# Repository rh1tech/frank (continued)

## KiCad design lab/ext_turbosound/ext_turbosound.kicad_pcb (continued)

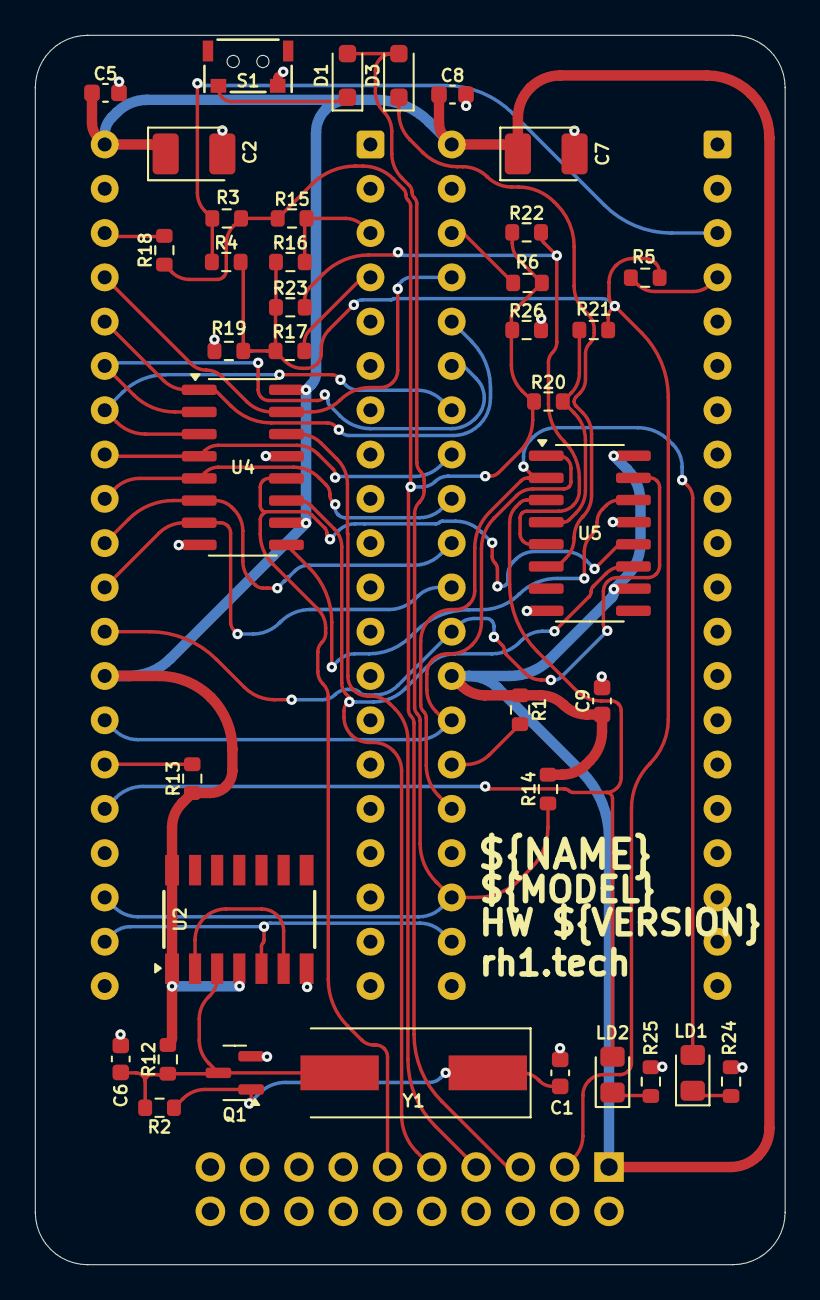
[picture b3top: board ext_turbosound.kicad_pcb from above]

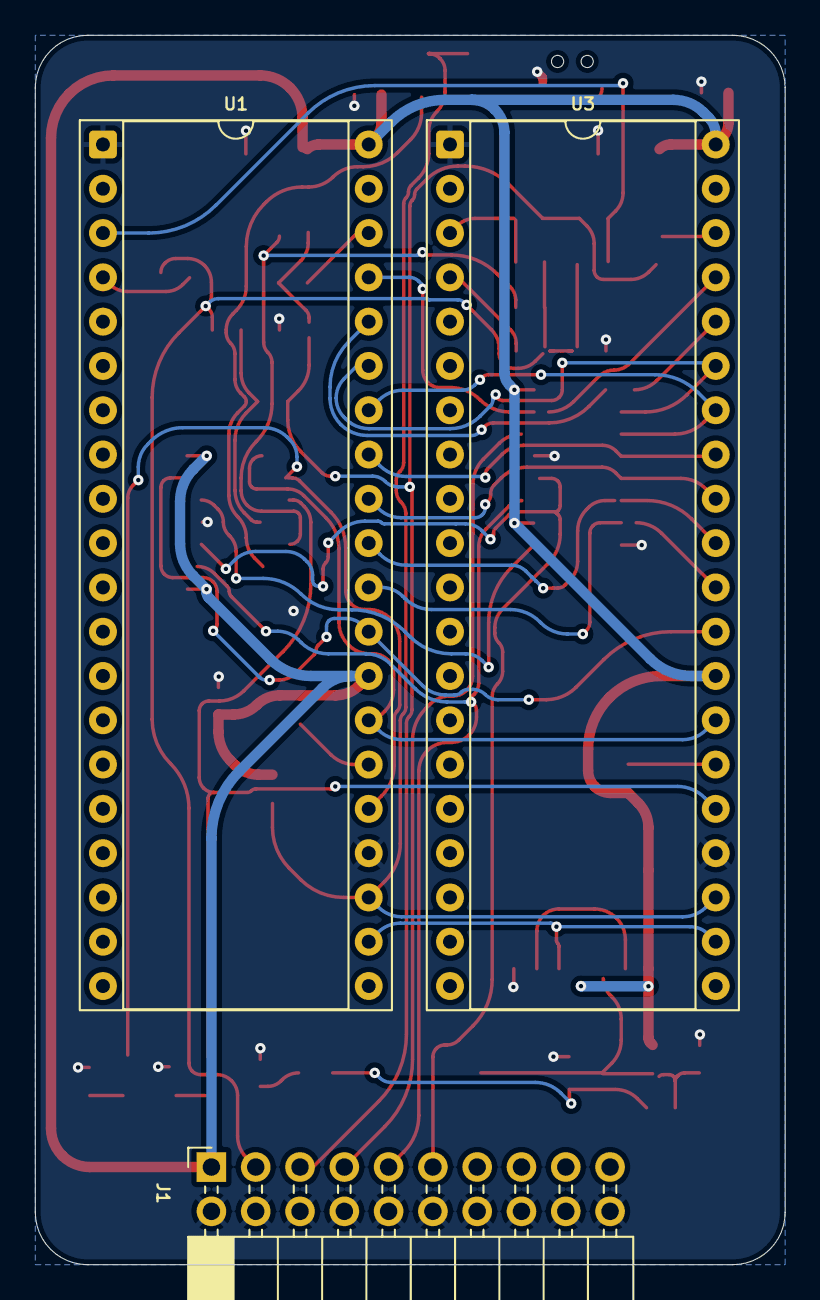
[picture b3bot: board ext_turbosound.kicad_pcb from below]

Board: 2 copper layers, 43.0 x 70.5 mm, 41 parts (3 on the bottom side), 39 nets.

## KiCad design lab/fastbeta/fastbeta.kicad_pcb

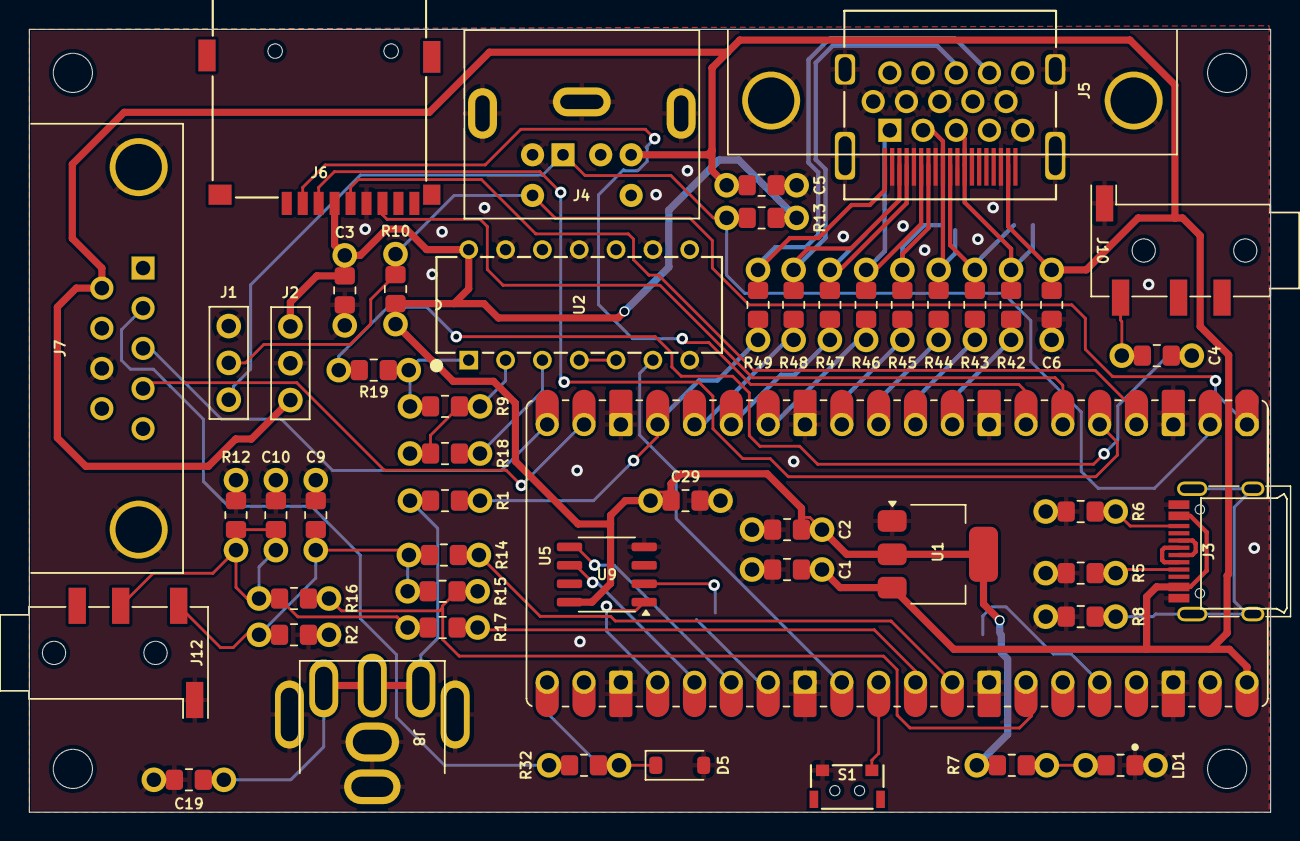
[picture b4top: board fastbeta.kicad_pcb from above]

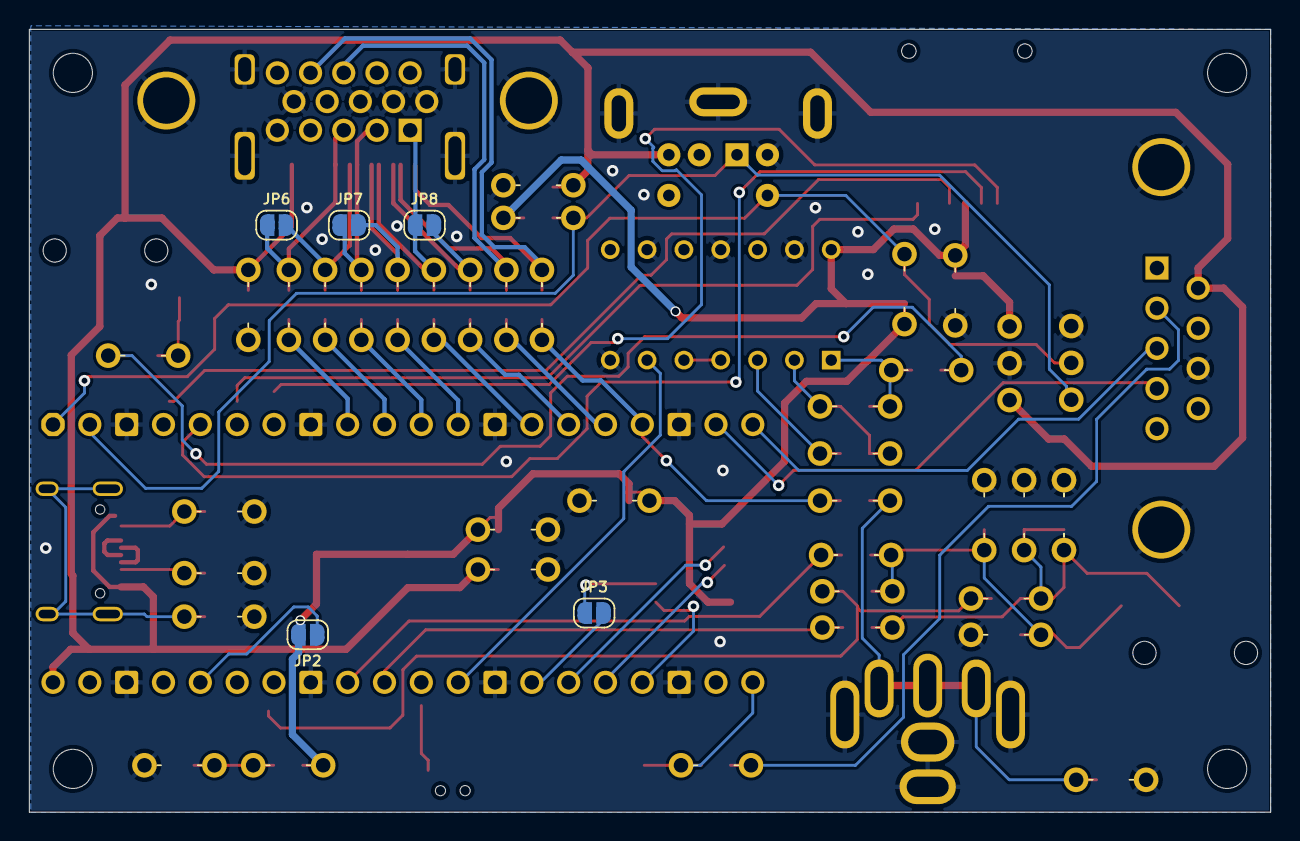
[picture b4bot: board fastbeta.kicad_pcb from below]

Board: 2 copper layers, 85.6 x 54.0 mm, 62 parts (5 on the bottom side), 55 nets.

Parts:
C1, C2: 10u; Combined 0805 CR
C3, C4, C5, C6, C29: 100n; Combined 0805 CR
C9, C10: 10n; Combined 0805 CR
C19: 470pF; Combined 0805 CR
D5: 3V3; Diode (SOD-123)
H1, H2, H3, H4: Hole 2.7mm; Mounting Hole (2.7mm)
J1, J2: Pin Header 1x03; Pin Header (1x03)
J3: USB4215; USB Type C
J4: MDC-036; MiniDIN (6 Pin, female)
J5: D-SUB 15 Female; D-SUB (15 pin, female)
J6: 104031-0811; MicroSD (SMD, long)
J7: D-SUB 9 Male; D-SUB (9 pin, male, top mount)
J8: RCA-103; RCA
J9: DC3RX19JA2; HDMI (female)
J10, J12: PJ-320D; Jack (3.5mm, PJ-320D)
JP2, JP3, JP6, JP7, JP8: Jumper (Solder); Jumper (solder)
LD1: Green; Combined 0805 LD
R1: 75R; Combined 0805 RE
R2, R12: 330R; Combined 0805 RE
R5, R6: 5.1K; Combined 0805 RE
R7, R10, R13, R14, R17, R32: 1K; Combined 0805 RE
R8: 1M; Combined 0805 RE
R9, R18: 100K; Combined 0805 RE
R15, R16: 2K; Combined 0805 RE
R19: 4.7K; Combined 0805 RE
R42, R43, R44, R45, R46, R47, R48, R49: 220R; Combined 0805 RE
S1: Reset RP2530A; TACT-SIDE-4623
U1: NCP1117 3.3; SOT-223
U2: N14; CD4069UBE
U5: Rasberry Pi Pico; Raspberry Pi Pico
U9: ESP-PSRAM32; SO-8

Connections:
+3V3: C2.1, C3.2, C29.1, J2.1, J6.4 (VDD), JP2.2 (B), R7.2, R10.2, R13.2, U1.2 (VO), U2.14 (VDD), U9.8 (VCC)
/Audio/L: C9.1, J12.T, R2.1, R14.1, R15.1
/Audio/R: C10.1, J12.R, R12.1, R16.1, R17.1
/PGPIO0: J1.2, J4.5, R10.1, U5.1 (GPIO0)
/PGPIO1: J1.3, J4.1, R13.1, U5.2 (GPIO1)
/PGPIO2: J6.5 (CLK), U5.4 (GPIO2)
/PGPIO3: J6.3 (CMD), U5.5 (GPIO3)
/PGPIO4: J6.7 (DAT0), U5.6 (GPIO4)
/PGPIO5: J6.2 (DAT3/CD), U5.7 (GPIO5)
/PGPIO6: R42.2, U5.9 (GPIO6)
/PGPIO7: R43.2, U5.10 (GPIO7)
/PGPIO8: R44.2, U5.11 (GPIO8)
/PGPIO9: R45.2, U5.12 (GPIO9)
/PGPIO10: R46.2, U5.14 (GPIO10)
/PGPIO11: R47.2, U5.15 (GPIO11)
/PGPIO12: R48.2, U5.16 (GPIO12)
/PGPIO13: R1.1, R49.2, U5.17 (GPIO13)
/PGPIO14: J7.4, U5.19 (GPIO14)
/PGPIO15: J7.3, U5.20 (GPIO15)
/PGPIO16: D5.1 (K), R32.1, U5.21 (GPIO16)
/PGPIO18: U5.24 (GPIO18), U9.1 (~CE)
/PGPIO19: U5.25 (GPIO19), U9.6 (SCLK)
/PGPIO20: U5.26 (GPIO20), U9.5 (SI/SIO)
/PGPIO21: JP3.2 (B), U5.27 (GPIO21)
/PGPIO22: U2.6 (I=*C), U5.29 (GPIO22)
/PGPIO26: R17.2, U5.31 (GPIO26_ADC0)
/PGPIO27: R14.2, U5.32 (GPIO27_ADC1)
/PGPIO28: R15.2, R16.2, U5.34 (GPIO28_ADC2)
/PRUN: S1.1, U5.30 (RUN)
/Power/D+: J3.6 (DP1), J3.8 (DP2)
/Power/D-: J3.5 (DN2), J3.7 (DN1)
/Tape In/TAPE: C4.2, J10.T
/Video Out/VGA_B: J5.3, J9.12 (CLKN), JP6.1 (A), R42.1
/Video Out/VGA_BH: J9.10 (CLKP), JP6.2 (B), R43.1
/Video Out/VGA_G: J5.2, J9.9 (D0N), JP7.1 (A), R44.1
/Video Out/VGA_GH: J9.7 (D0P), JP7.2 (B), R45.1
/Video Out/VGA_HS: J5.13, J9.3 (D2N), R48.1
/Video Out/VGA_R: J5.1, J9.6 (D1N), JP8.1 (A), R46.1
/Video Out/VGA_RH: J9.4 (D1P), JP8.2 (B), R47.1
/Video Out/VGA_VS: J5.14, J9.1 (D2P), R49.1
GND: C1.2, C2.2, C3.1, C5.2, C6.2, C9.2, C10.2, C19.2, C29.2, D5.2 (A), J1.1, J2.2, J3.1 (GND), J3.12 (GND), J4.3, J5.0, J5.5, J5.6, J5.7, J5.8, J5.10, J6.6 (VSS), J7.8, J8.2, J9.2 (G_D2), J9.5 (G_D1), J9.8 (G_D0), J9.11 (G_CLK), J9.17 (G_DDC/CEC), J9.20 (SHIELD1), J9.21 (SHIELD2), J9.22 (SHIELD3), J9.23 (SHIELD4), J10.S, J12.S, LD1.1 (K), R2.2, R5.1, R6.1, R8.2, R12.2, S1.2, U1.1 (GND), U2.7 (VSS), U2.9 (D14), U2.11 (E), U2.13 (F), U5.3 (GND), U5.8 (GND), U5.13 (GND), U5.18 (GND), U5.23 (GND), U5.28 (GND), U5.33 (AGND), U5.38 (GND), U9.4 (VSS)
unnamed: C4.1, R19.2
unnamed: J3.4 (CC1), R5.2
unnamed: J3.10 (CC2), R6.2
unnamed: J3.13 (SHIELD), R8.1
unnamed: J7.2, R32.2
unnamed: C19.1, J8.1, R1.2
unnamed: JP2.1 (A), U5.36 (3V3)
unnamed: JP3.1 (A), U9.2 (SO/SIO)
unnamed: LD1.2 (A), R7.1
unnamed: R9.2, R19.1, U2.1 (A)
unnamed: R18.1, U2.3 (B)
unnamed: U2.4 (H=*B), U2.5 (C)
unnamed: R9.1, R18.2, U2.2 (G-*A)
VBUS: C1.1, C5.1, C6.1, J2.3, J3.2 (VBUS), J3.11 (VBUS), J4.4, J7.6, J9.18 (+5V), U1.3 (VI), U5.40 (VBUS)

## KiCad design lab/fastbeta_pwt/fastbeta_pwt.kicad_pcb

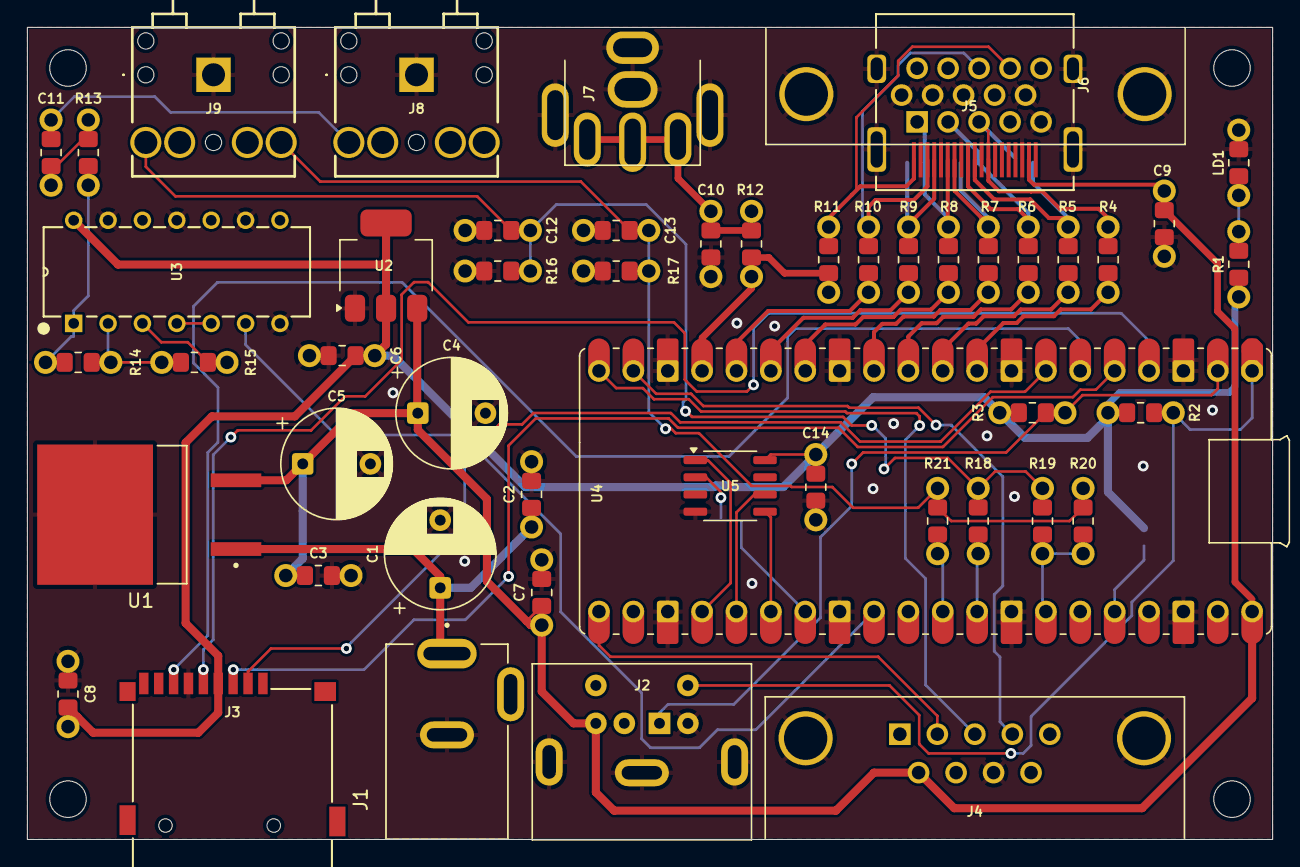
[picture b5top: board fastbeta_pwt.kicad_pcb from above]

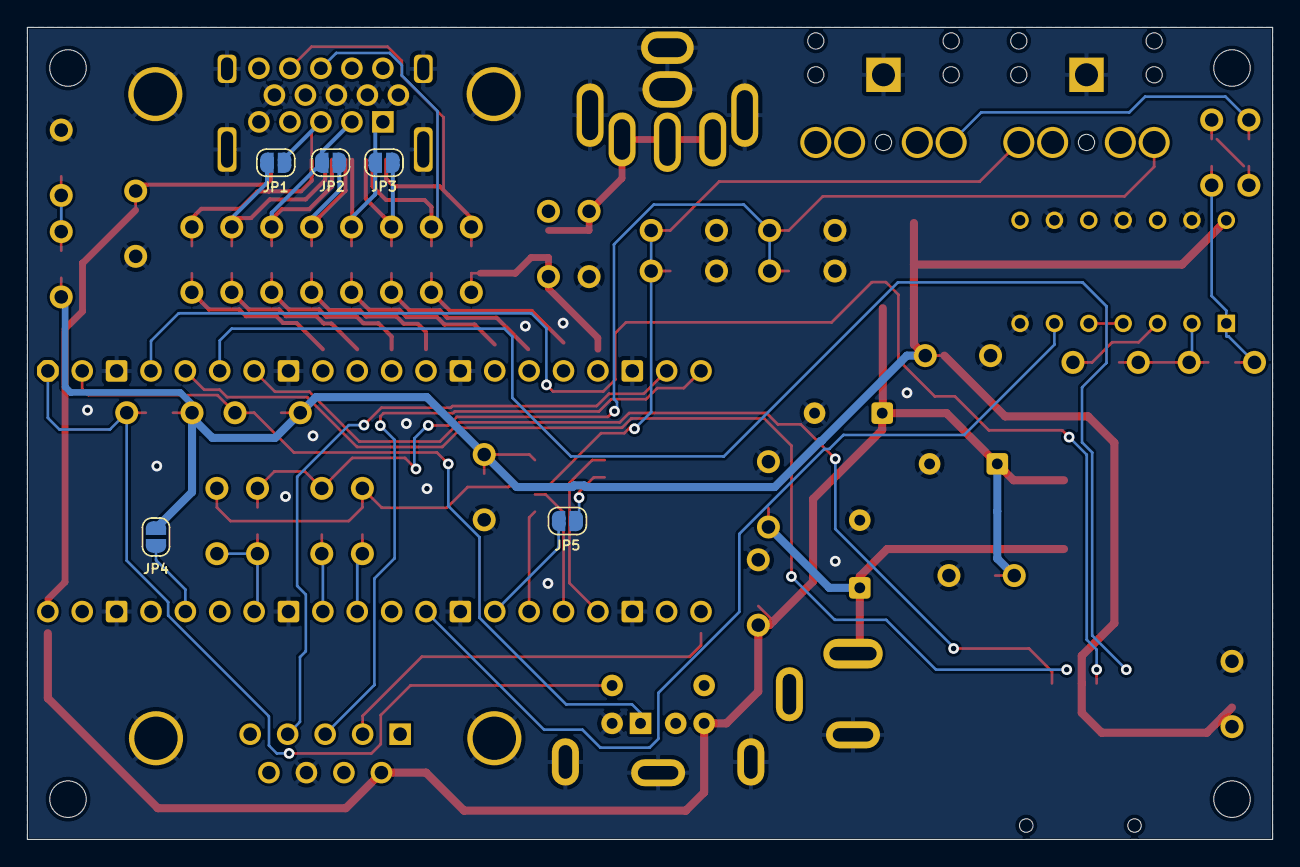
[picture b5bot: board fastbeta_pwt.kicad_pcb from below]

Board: 2 copper layers, 92.0 x 60.0 mm, 59 parts (5 on the bottom side), 49 nets.

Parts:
C1, C4, C5: 470u; Capacitor (radial, polar, D8.0mm, P5.00mm)
C2, C3, C7, C8, C9, C11, C14: 100n; Combined 0805 CR
C6: 10u; Combined 0805 CR
C10: 470pF; Combined 0805 CR
C12, C13: 10n; Combined 0805 CR
H1, H2, H3, H4: Hole 2.7mm; Mounting Hole (2.7mm)
J1: DC-005-5A-2.0; XKB_DC-005-5A-2.0
J2: MDC-036; MiniDIN (6 Pin, female)
J3: 104031-0811; MicroSD (SMD, long)
J4: D-SUB 9 Male; D-SUB (9 pin, male, top mount)
J5: DC3RX19JA2; HDMI (female)
J6: D-SUB 15 Female; D-SUB (15 pin, female)
J7: RCA-103; RCA
J8, J9: SJ1-3525N; SJ13525N
JP1, JP2, JP3, JP4, JP5: Jumper (Solder); Jumper (solder)
LD1: Green; Combined 0805 LD
R1, R2, R3, R18, R21: 1K; Combined 0805 RE
R4, R5, R6, R7, R8, R9, R10, R11: 220R; Combined 0805 RE
R12: 75R; Combined 0805 RE
R13: 4.7K; Combined 0805 RE
R14, R15: 100K; Combined 0805 RE
R16, R17: 330R; Combined 0805 RE
R19, R20: 2K; Combined 0805 RE
U1: L7805; TO254P1542X460-3N
U2: AMS1117 3.3; SOT-223
U3: CD4069UBE
U4: Rasberry Pi Pico; Raspberry Pi Pico
U5: ESP-PSRAM32; SO-8

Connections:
+3V3: C6.1, C8.2, C14.1, J3.4 (VDD), JP4.2 (B), R1.2, R2.2, R3.2, U2.2 (VO), U3.14 (VDD), U5.8 (VCC)
/Audio/L: C12.1, J9.2 (TIP), R16.1, R18.1, R19.1
/Audio/R: C13.1, J9.3 (RING), R17.1, R20.1, R21.1
/PGPIO0: J2.5, R2.1, U4.1 (GPIO0)
/PGPIO1: J2.1, R3.1, U4.2 (GPIO1)
/PGPIO2: J3.5 (CLK), U4.4 (GPIO2)
/PGPIO3: J3.3 (CMD), U4.5 (GPIO3)
/PGPIO4: J3.7 (DAT0), U4.6 (GPIO4)
/PGPIO5: J3.2 (DAT3/CD), U4.7 (GPIO5)
/PGPIO6: R4.2, U4.9 (GPIO6)
/PGPIO7: R5.2, U4.10 (GPIO7)
/PGPIO8: R6.2, U4.11 (GPIO8)
/PGPIO9: R7.2, U4.12 (GPIO9)
/PGPIO10: R8.2, U4.14 (GPIO10)
/PGPIO11: R9.2, U4.15 (GPIO11)
/PGPIO12: R10.2, U4.16 (GPIO12)
/PGPIO13: R11.2, R12.1, U4.17 (GPIO13)
/PGPIO14: J4.4, U4.19 (GPIO14)
/PGPIO15: J4.3, U4.20 (GPIO15)
/PGPIO16: J4.2, U4.21 (GPIO16)
/PGPIO18: U4.24 (GPIO18), U5.1 (~CE)
/PGPIO19: U4.25 (GPIO19), U5.6 (SCLK)
/PGPIO20: U4.26 (GPIO20), U5.5 (SI/SIO)
/PGPIO21: JP5.2 (B), U4.27 (GPIO21)
/PGPIO22: U3.6 (I=*C), U4.29 (GPIO22)
/PGPIO26: R21.2, U4.31 (GPIO26_ADC0)
/PGPIO27: R18.2, U4.32 (GPIO27_ADC1)
/PGPIO28: R19.2, R20.2, U4.34 (GPIO28_ADC2)
/Tape In/TAPE: C11.2, J8.2 (TIP)
/Video Out/VGA_B: J5.12 (CLKN), J6.3, JP1.1 (A), R4.1
/Video Out/VGA_BH: J5.10 (CLKP), JP1.2 (B), R5.1
/Video Out/VGA_G: J5.9 (D0N), J6.2, JP2.1 (A), R6.1
/Video Out/VGA_GH: J5.7 (D0P), JP2.2 (B), R7.1
/Video Out/VGA_HS: J5.3 (D2N), J6.13, R10.1
/Video Out/VGA_R: J5.6 (D1N), J6.1, JP3.1 (A), R8.1
/Video Out/VGA_RH: J5.4 (D1P), JP3.2 (B), R9.1
/Video Out/VGA_VS: J5.1 (D2P), J6.14, R11.1
GND: C1.2, C2.2, C3.2, C4.2, C5.2, C6.2, C7.2, C8.1, C9.2, C10.2, C12.2, C13.2, C14.2, J1.2, J2.3, J3.6 (VSS), J4.8, J5.2 (G_D2), J5.5 (G_D1), J5.8 (G_D0), J5.11 (G_CLK), J5.17 (G_DDC/CEC), J5.20 (SHIELD1), J5.21 (SHIELD2), J5.22 (SHIELD3), J5.23 (SHIELD4), J6.0, J6.5, J6.6, J6.7, J6.8, J6.10, J7.2, J8.1 (SLEEVE), J9.1 (SLEEVE), LD1.1 (K), R16.2, R17.2, U1.2 (GND), U2.1 (GND), U3.7 (VSS), U3.9 (D14), U3.11 (E), U3.13 (F), U4.3 (GND), U4.8 (GND), U4.13 (GND), U4.18 (GND), U4.23 (GND), U4.28 (GND), U4.33 (AGND), U4.38 (GND), U5.4 (VSS)
unnamed: C11.1, R13.2
unnamed: C10.1, J7.1, R12.2
unnamed: JP4.1 (A), U4.36 (3V3)
unnamed: JP5.1 (A), U5.2 (SO/SIO)
unnamed: LD1.2 (A), R1.1
unnamed: C1.1, C2.1, J1.1, U1.1 (IN)
unnamed: R13.1, R14.2, U3.1 (A)
unnamed: R15.1, U3.3 (B)
unnamed: U3.4 (H=*B), U3.5 (C)
unnamed: R14.1, R15.2, U3.2 (G-*A)
VBUS: C3.1, C4.1, C5.1, C7.1, C9.1, J2.4, J4.6, J5.18 (+5V), U1.3 (OUT), U2.3 (VI), U4.40 (VBUS)

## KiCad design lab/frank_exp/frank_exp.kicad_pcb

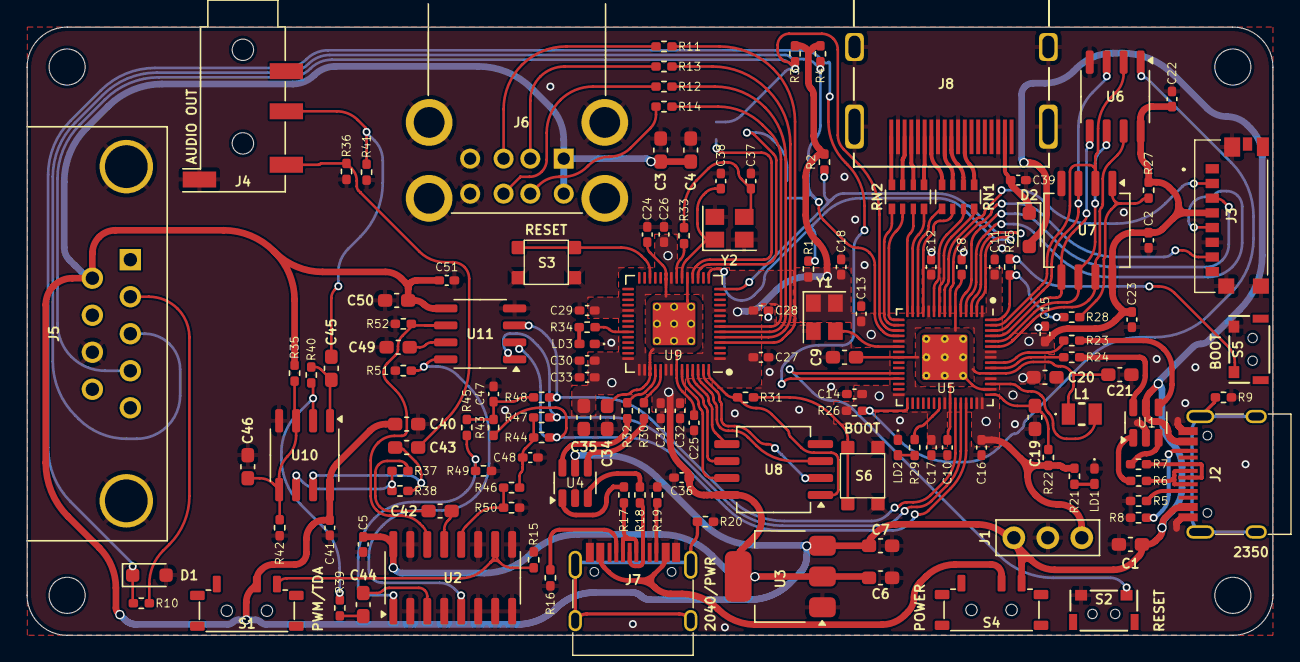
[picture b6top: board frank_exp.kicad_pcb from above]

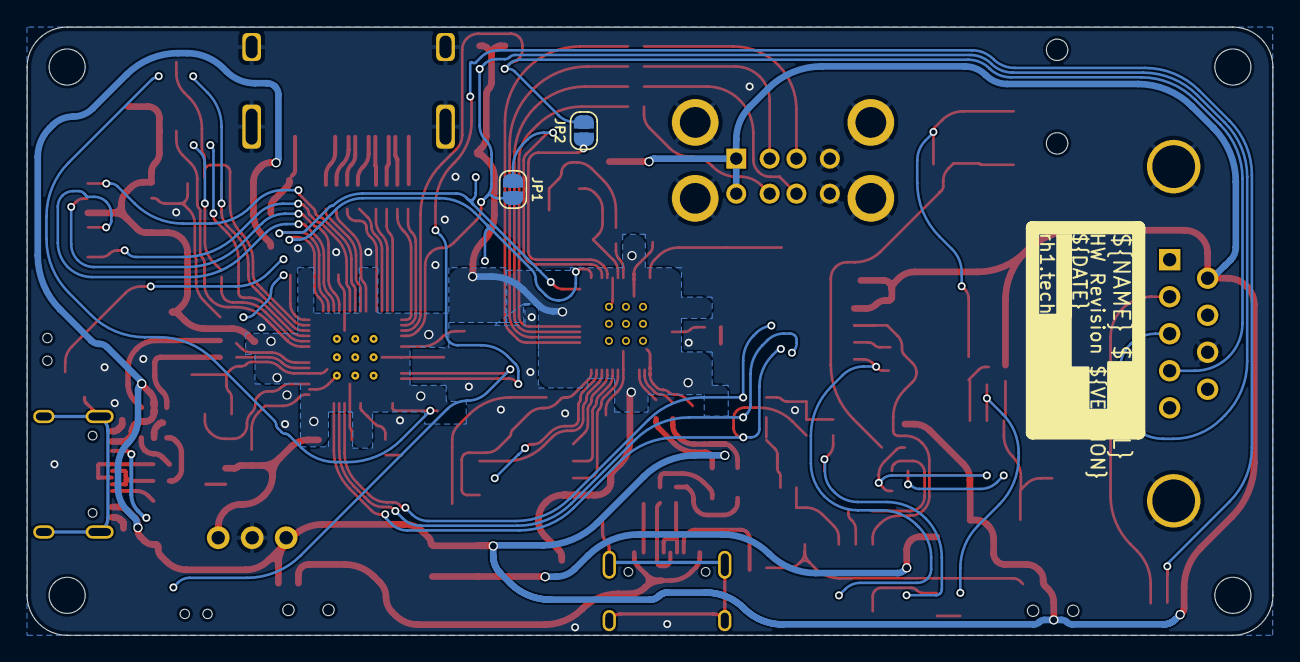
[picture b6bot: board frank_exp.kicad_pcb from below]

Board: 2 copper layers, 93.2 x 45.5 mm, 144 parts (2 on the bottom side), 116 nets.

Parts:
C1, C3, C4, C6, C7, C40, C42, C43, C44, C45, C46, C49, C50: 10u; Capacitor (0603)
C2, C5, C8, C10, C11, C12, C13, C14, C15, C16, C17, C18, C22, C23, C24, C25, C26, C27, C28, C29, C30, C31, C32, C33, C36, C39, C41, C51: 100n; Capacitor (0402)
C9, C19, C20, C21: 4.7u; Capacitor (0603)
C34, C35: 1u; Capacitor (0603)
C37, C38: 15p; Capacitor (0402)
C47, C48: 47n; Capacitor (0402)
D1: 3V3; Diode (SOD-323)
D2: 1N5819WS; Diode (SOD-323)
H1, H2, H3, H4: MountingHole; Mounting Hole (2.7mm)
J1: PWR; Pin Header (1x03)
J2, J7: USB4215-03-A; USB Type C
J3: 0475710001; MicroSD (SMD, short)
J4: PJ-320D; Jack (3.5mm, PJ-320D)
J5: D-SUB 9 Male; D-SUB (9 pin, male, top mount)
J6: SS-52100-004; USB Type A (stacked)
J8: DC3RX19JA2; HDMI (female)
JP1: Mouse (DATA); Jumper (solder)
JP2: Mouse (CLK); Jumper (solder)
L1: 3.3u; Inductor (0806)
LD1: Power; LED (0402)
LD2, LD3: Blue; LED (0402)
R1, R2, R3, R4, R15, R26, R27, R35, R37, R39, R42, R45, R46: 10K; Resistor (0402)
R5, R8, R16, R19: 5.1K; Resistor (0402)
R6, R7, R11, R12, R13, R14, R17, R18: 22R; Resistor (0402)
R9, R20: 1M; Resistor (0402)
R10, R21, R25, R29, R31, R33, R34, R47, R48: 1K; Resistor (0402)
R22: 33R; Resistor (0402)
R23, R24, R30, R32: 27R; Resistor (0402)
R28: 0R; Resistor (0402)
R36, R41: 20K; Resistor (0402)
R38, R40: 47K; Resistor (0402)
R43, R44, R49, R50: 2K; Resistor (0402)
R51, R52: 470R; Resistor (0402)
RN1, RN2: 270R; Resistor Array (4x0603)
S1, S4: MSK12C02; Switch (MSK12C02)
S2: Reset RP2530A; TACT-SIDE-4623
S3: Reset RP2040; Button (SMD, 3x3mm, 1-1)
S5: Boot 2350; TACT-SIDE-4623
S6: Boot 2040; Button (SMD, 3x3mm, 1-1)
U1, U4: USBLC6-2SC6; SOT-23-6
U2: 74HC4052D; SOP-16
U3: NCP1117 3.3; SOT-223
U5: RP2350; QFN 60 (RP2350A)
U6: ESP-PSRAM32; SO-8
U7: W25Q128JVS; SOIC-8
U8: W25Q128JVSIQ; SOIC-8
U9: RP2040; QFN 56
U10: LM358; SO-8
U11: TDA1387T; SO-8
Y1: ASE-12MHz; Crystal (3225, active)
Y2: 12 MHz; Crystal (3225)

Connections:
+1V1: C8.1, C9.1, C10.1, C21.1, L1.1, U5.6 (DVDD), U5.23 (DVDD), U5.39 (DVDD), U5.50 (VREG_FB)
+3V3: C2.2, C5.2, C6.1, C11.1, C12.1, C13.1, C14.1, C15.1, C16.1, C17.1, C18.1, C20.1, C22.1, C23.1, C26.1, C27.1, C28.1, C29.1, C30.1, C31.1, C32.1, C33.1, C35.1, C36.1, J1.1, J3.P4 (VDD), R1.2, R2.2, R3.2, R4.2, R21.2, R22.1, R26.2, R27.1, U2.16 (VCC), U3.2 (VO), U5.1 (IOVDD), U5.11 (IOVDD), U5.20 (IOVDD), U5.30 (IOVDD), U5.38 (IOVDD), U5.44 (ADC_AVDD), U5.45 (IOVDD), U5.49 (VREG_VIN), U5.53 (USB_OTP_VDD), U5.54 (QSPI_IOVDD), U6.8 (VCC), U7.8 (VCC), U8.8 (VCC), U9.1 (IOVDD), U9.10 (IOVDD), U9.22 (IOVDD), U9.33 (IOVDD), U9.42 (IOVDD), U9.43 (ADC_AVDD), U9.44 (VREG_IN), U9.48 (USB_VDD), U9.49 (IOVDD), Y1.1 (EN), Y1.4 (Vdd)
/AMP_IN_L: C42.1, U2.13 (1Z)
/AMP_IN_R: C44.1, U2.3 (2Z)
/AUDIOSW: R15.2, S1.3 (A), U2.10 (S0)
/Audio Out/AMP_OUTL: C43.2, J4.T, R36.2
/Audio Out/AMP_OUTR: C45.2, J4.R, R41.2
/D+: R23.1, U1.4 (I/O2)
/D-: R24.1, U1.6 (I/O1)
/GPIO0: R1.1, U5.2 (GPIO0), U9.15 (GPIO12)
/GPIO1: R2.1, U5.3 (GPIO1), U9.14 (GPIO11)
/GPIO2: J3.P5 (CLK), U5.4 (GPIO2)
/GPIO3: J3.P3 (CMD), U5.5 (GPIO3)
/GPIO4: J3.P7 (DAT0), U5.7 (GPIO4)
/GPIO5: J3.P2 (CD/DAT3), U5.8 (GPIO5)
/GPIO6: RN1.4 (R4.1), U5.9 (GPIO6)
/GPIO7: RN1.3 (R3.1), U5.10 (GPIO7)
/GPIO8: RN1.2 (R2.1), U5.12 (GPIO8)
/GPIO9: RN1.1 (R1.1), U5.13 (GPIO9)
/GPIO10: RN2.4 (R4.1), U5.14 (GPIO10)
/GPIO11: RN2.3 (R3.1), U5.15 (GPIO11)
/GPIO12: RN2.2 (R2.1), U5.16 (GPIO12)
/GPIO13: RN2.1 (R1.1), U5.17 (GPIO13)
/GPIO14: J5.4, JP2.2 (B), R3.1, U5.18 (GPIO14)
/GPIO15: J5.3, JP1.2 (B), R4.1, U5.19 (GPIO15)
/GPIO16: D1.1 (K), R10.1, U5.27 (GPIO16)
/GPIO19: R26.1, U5.31 (GPIO19), U6.1 (~CE)
/GPIO26: R48.2, U5.40 (GPIO26_ADC0), U11.3 (DATA)
/GPIO27: R47.2, U5.41 (GPIO27_ADC1), U11.1 (SCLK)
/GPIO28: R43.1, R44.1, U5.42 (GPIO28_ADC2), U11.2 (LRCK)
/MS_CLK: JP2.1 (A), U9.18 (GPIO15)
/MS_DATA: JP1.1 (A), U9.17 (GPIO14)
/PWM_OUT_L: R46.2, R50.1, U2.12 (1Y0)
/PWM_OUT_R: R45.2, R49.1, U2.1 (2Y0)
/RP2_D+: R30.1, U4.4 (I/O2)
/RP2_D-: R32.1, U4.6 (I/O1)
/RP2_GPIO2: R11.1, U9.4 (GPIO2)
/RP2_GPIO3: R13.1, U9.5 (GPIO3)
/RP2_GPIO4: R12.1, U9.6 (GPIO4)
/RP2_GPIO5: R14.1, U9.7 (GPIO5)
/RP2_RUN: S3.1, U9.26 (RUN)
/RP2040/GPIO25: R34.2, U9.37 (GPIO25)
/RP2040/QSPI_SCLK: U8.6 (CLK), U9.52 (QSPI_SCLK)
/RP2040/QSPI_SD0: U8.5 (DI(IO0)), U9.53 (QSPI_SD0)
/RP2040/QSPI_SD1: U8.2 (DO(IO1)), U9.55 (QSPI_SD1)
/RP2040/QSPI_SD2: U8.3 (IO2), U9.54 (QSPI_SD2)
/RP2040/QSPI_SD3: U8.7 (IO3), U9.51 (QSPI_SD3)
/RP2040/QSPI_SS: R31.1, U8.1 (~CS), U9.56 (QSPI_SS)
/RP2040/XIN: C38.1, U9.20 (XIN), Y2.1
/RP2040/XOUT: R33.1, U9.21 (XOUT)
/RP2350A/FLASH_SS: R27.2, R28.2, U7.1 (~CS)
/RP2350A/QSPI_SCLK: U5.56 (QSPI_SCLK), U6.6 (SCLK), U7.6 (CLK)
/RP2350A/QSPI_SD0: U5.57 (QSPI_SD0), U6.5 (SI/SIO), U7.5 (DI(IO0))
/RP2350A/QSPI_SD1: U5.59 (QSPI_SD1), U6.2 (SO/SIO), U7.2 (DO(IO1))
/RP2350A/QSPI_SD2: U5.58 (QSPI_SD2), U6.3 (SIO2), U7.3 (IO2)
/RP2350A/QSPI_SD3: U5.55 (QSPI_SD3), U6.7 (SIO3), U7.7 (IO3)
/RP2350A/QSPI_SS: R25.1, R28.1, U5.60 (QSPI_SS)
/RP2350A/VREG_AVDD: C19.1, R22.2, U5.46 (VREG_AVDD)
/RP2350A/VREG_LX: L1.2, U5.48 (VREG_LX)
/RP2350A/XIN: U5.21 (XIN), Y1.3 (OUT)
/RP2350A/~USB_BOOT: R25.2, S5.2
/RUN: S2.1, U5.26 (RUN)
/TDA_L: R52.2, U2.14 (1Y1), U11.6 (A_LEFT)
/TDA_R: R51.1, U2.5 (2Y1), U11.8 (A_RIGHT)
GND: C1.2, C2.1, C3.2, C4.2, C5.1, C6.2, C7.2, C8.2, C9.2, C10.2, C11.2, C12.2, C13.2, C14.2, C15.2, C16.2, C17.2, C18.2, C19.2, C20.2, C21.2, C22.2, C23.2, C24.2, C25.2, C26.2, C27.2, C28.2, C29.2, C30.2, C31.2, C32.2, C33.2, C34.2, C35.2, C36.2, C37.2, C38.2, C39.2, C40.1, C41.1, C46.1, C47.2, C48.2, C49.2, C50.2, C51.2, D1.2 (A), J1.2, J2.1 (GND), J2.12 (GND), J3.G1 (GND_1), J3.G2 (GND_2), J3.G3 (GND_3), J3.P6 (VSS), J4.S, J5.8, J6.4 (GND1), J6.8 (GND2), J6.9 (Shield), J7.1 (GND), J7.12 (GND), J8.2 (G_D2), J8.5 (G_D1), J8.8 (G_D0), J8.11 (G_CLK), J8.17 (G_DDC/CEC), J8.20 (SHIELD1), J8.21 (SHIELD2), J8.22 (SHIELD3), J8.23 (SHIELD4), LD1.1 (K), LD2.1 (K), LD3.1 (K), R5.1, R8.1, R9.2, R15.1, R16.1, R19.1, R20.2, R36.1, R41.1, R42.1, R49.2, R50.2, R51.2, R52.1, S2.2, S3.2, S5.1, S6.2, U1.2 (GND), U2.2 (2Y2), U2.4 (2Y3), U2.6 (~E), U2.7 (VEE), U2.8 (GND), U2.9 (S1), U2.11 (1Y3), U2.15 (1Y2), U3.1 (GND), U4.2 (GND), U5.47 (VREG_PGND), U5.61 (GND), U6.4 (VSS), U7.4 (GND), U8.4 (GND), U9.19 (TESTEN), U9.57 (GND), U10.4 (V-), U11.4 (AGND), Y1.2 (GND), Y2.2, Y2.4
GPIO25: R29.2, U5.37 (GPIO25)
unnamed: C37.1, R33.2, Y2.3
unnamed: C42.2, R37.2
unnamed: C43.1, R38.1, U10.7
unnamed: C44.2, R39.2
unnamed: C45.1, R40.1, U10.1
unnamed: C47.1, R43.2, R45.1, R48.1
unnamed: C48.1, R44.2, R46.1, R47.1
unnamed: C39.1, D2.1 (K), J8.18 (+5V)
unnamed: J2.4 (CC1), R5.2
unnamed: J2.10 (CC2), R8.2
unnamed: J2.5 (DN2), J2.7 (DN1), R6.2
unnamed: J2.6 (DP1), J2.8 (DP2), R7.2
unnamed: J2.13 (SHIELD), R9.1
unnamed: J5.2, R10.2
unnamed: J6.3 (D1+), R11.2
unnamed: J6.2 (D1-), R13.2
unnamed: J6.7 (D2+), R12.2
unnamed: J6.6 (D2-), R14.2
unnamed: J7.4 (CC1), R16.2
unnamed: J7.10 (CC2), R19.2
unnamed: J7.5 (DN2), J7.7 (DN1), R17.2
unnamed: J7.6 (DP1), J7.8 (DP2), R18.2
unnamed: J7.13 (SHIELD), R20.1
unnamed: J8.12 (CLKN), RN1.5 (R4.2)
unnamed: J8.10 (CLKP), RN1.6 (R3.2)
unnamed: J8.9 (D0N), RN1.7 (R2.2)
unnamed: J8.7 (D0P), RN1.8 (R1.2)
unnamed: J8.6 (D1N), RN2.5 (R4.2)
unnamed: J8.4 (D1P), RN2.6 (R3.2)
unnamed: J8.3 (D2N), RN2.7 (R2.2)
unnamed: J8.1 (D2P), RN2.8 (R1.2)
unnamed: LD1.2 (A), R21.1
unnamed: LD2.2 (A), R29.1
unnamed: LD3.2 (A), R34.1
unnamed: R6.1, U1.1 (I/O1)
unnamed: R7.1, U1.3 (I/O2)
unnamed: R17.1, U4.1 (I/O1)
unnamed: R18.1, U4.3 (I/O2)
unnamed: R31.2, S6.1
unnamed: J7.2 (VBUS), J7.11 (VBUS), S4.2 (B)
unnamed: R24.2, U5.51 (USB_DM)
unnamed: R23.2, U5.52 (USB_DP)
unnamed: R32.2, U9.46 (USB_DM)
unnamed: R30.2, U9.47 (USB_DP)
unnamed: C24.1, C25.1, C34.1, U9.23 (DVDD), U9.45 (VREG_VOUT), U9.50 (DVDD)
unnamed: C46.2, R35.1, R42.2, U10.3 (+), U10.5 (+)
unnamed: R39.1, R40.2, U10.2 (-)
unnamed: R37.1, R38.2, U10.6 (-)
unnamed: C49.1, U11.7 (FLT)
VBUS: C1.1, C3.1, C4.1, C7.1, C40.2, C41.2, C50.1, C51.1, D2.2 (A), J1.3, J2.2 (VBUS), J2.11 (VBUS), J5.6, J6.1 (VBUS1), J6.5 (VBUS2), R35.2, S1.2 (B), S4.3 (A), U1.5 (VBUS), U3.3 (VI), U4.5 (VBUS), U10.8 (V+), U11.5 (VA)
